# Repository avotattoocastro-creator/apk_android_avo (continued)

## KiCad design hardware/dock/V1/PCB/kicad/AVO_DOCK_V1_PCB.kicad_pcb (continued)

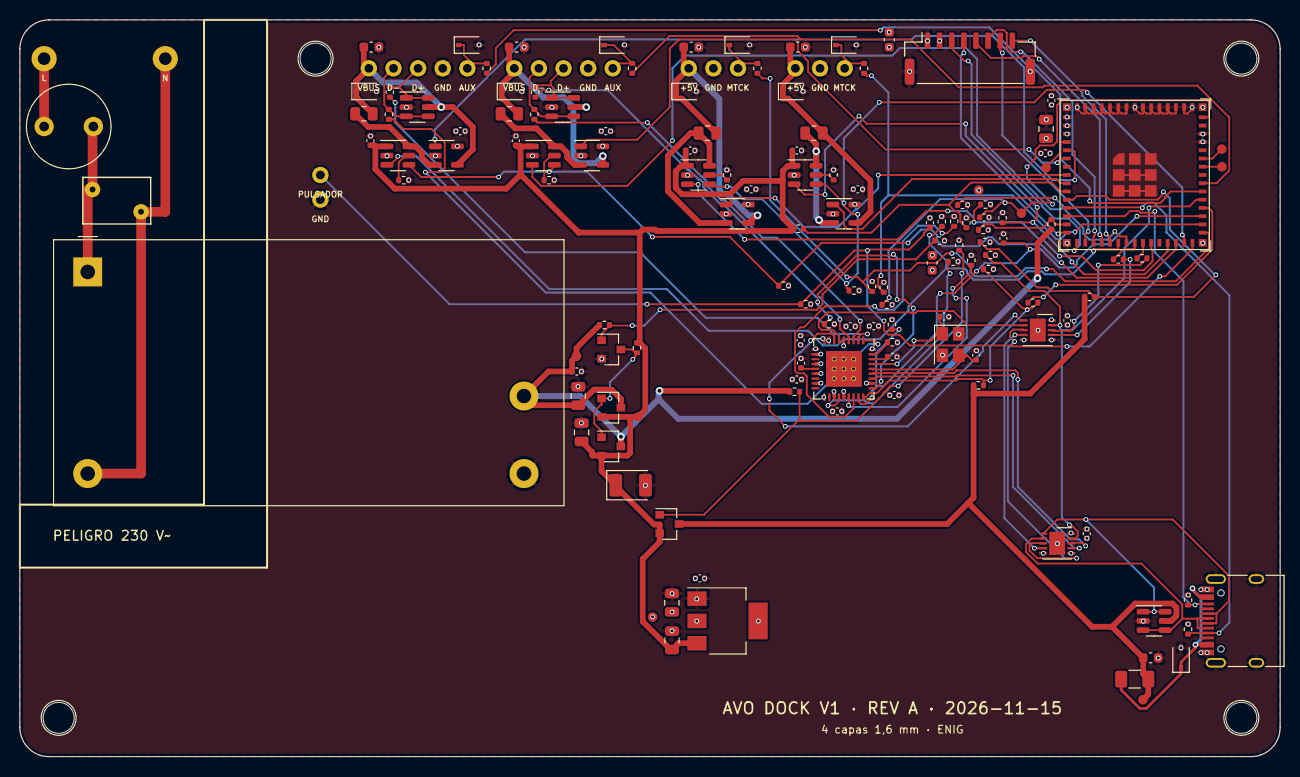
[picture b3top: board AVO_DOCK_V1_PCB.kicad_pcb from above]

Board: 4 copper layers, 130.0 x 76.0 mm, 160 parts (0 on the bottom side), 91 nets.

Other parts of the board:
H1, H2, H3, H4: TALADRO M3; AVO_Taladro_NPTH_D3.2

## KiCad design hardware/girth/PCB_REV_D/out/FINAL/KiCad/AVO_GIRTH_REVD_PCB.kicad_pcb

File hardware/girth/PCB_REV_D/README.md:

# AVO GIRTH · PCB REV D (cincha: ESP32-C6 + LSM6DSV16X + MMC5983MA + ADS1292)

Placa de 46 × 30 mm, 4 capas, generada desde Python (`fuente/`), ruteada en el CI (Freerouting 1.9) y completada con
`fuente/repair.py`. Comprobada en el CI con KiCad 9 (DRC, ERC y paridad).

- **Ficheros para JLCPCB:** `out/FINAL/` (Gerber zip, BOM, CPL, STEP, informe, SHA256SUMS).
- **Informe y decisiones:** `DOCS/INFORME_PCB_REV_D.md`. **Batería:** `DOCS/CONSUMO_BATERIA.md` (1000 mAh).
- **Firmware:** `firmware/girth/V0_6_0`.

Flujo:
1. `python3 fuente/place_revd.py` y después `python3 fuente/build.py`. Así se genera la placa de colocación.
2. El CI (`build-girth-pcb-revd.yml`) rutea y comprueba.
3. `python3 fuente/repair.py` completa las conexiones que falten y escribe `kicad/*_ruteado.kicad_pcb`, que el CI usa
   tal cual. Con `--src` se parte de otra placa y con `--rip` se rehacen redes.
4. `fuente/stitch_gnd.py --write` añade vías de cosido en las islas del relleno de F.Cu.

**Estado: VERIFICADO POR SOFTWARE · NO VERIFICADO EN HARDWARE REAL.**

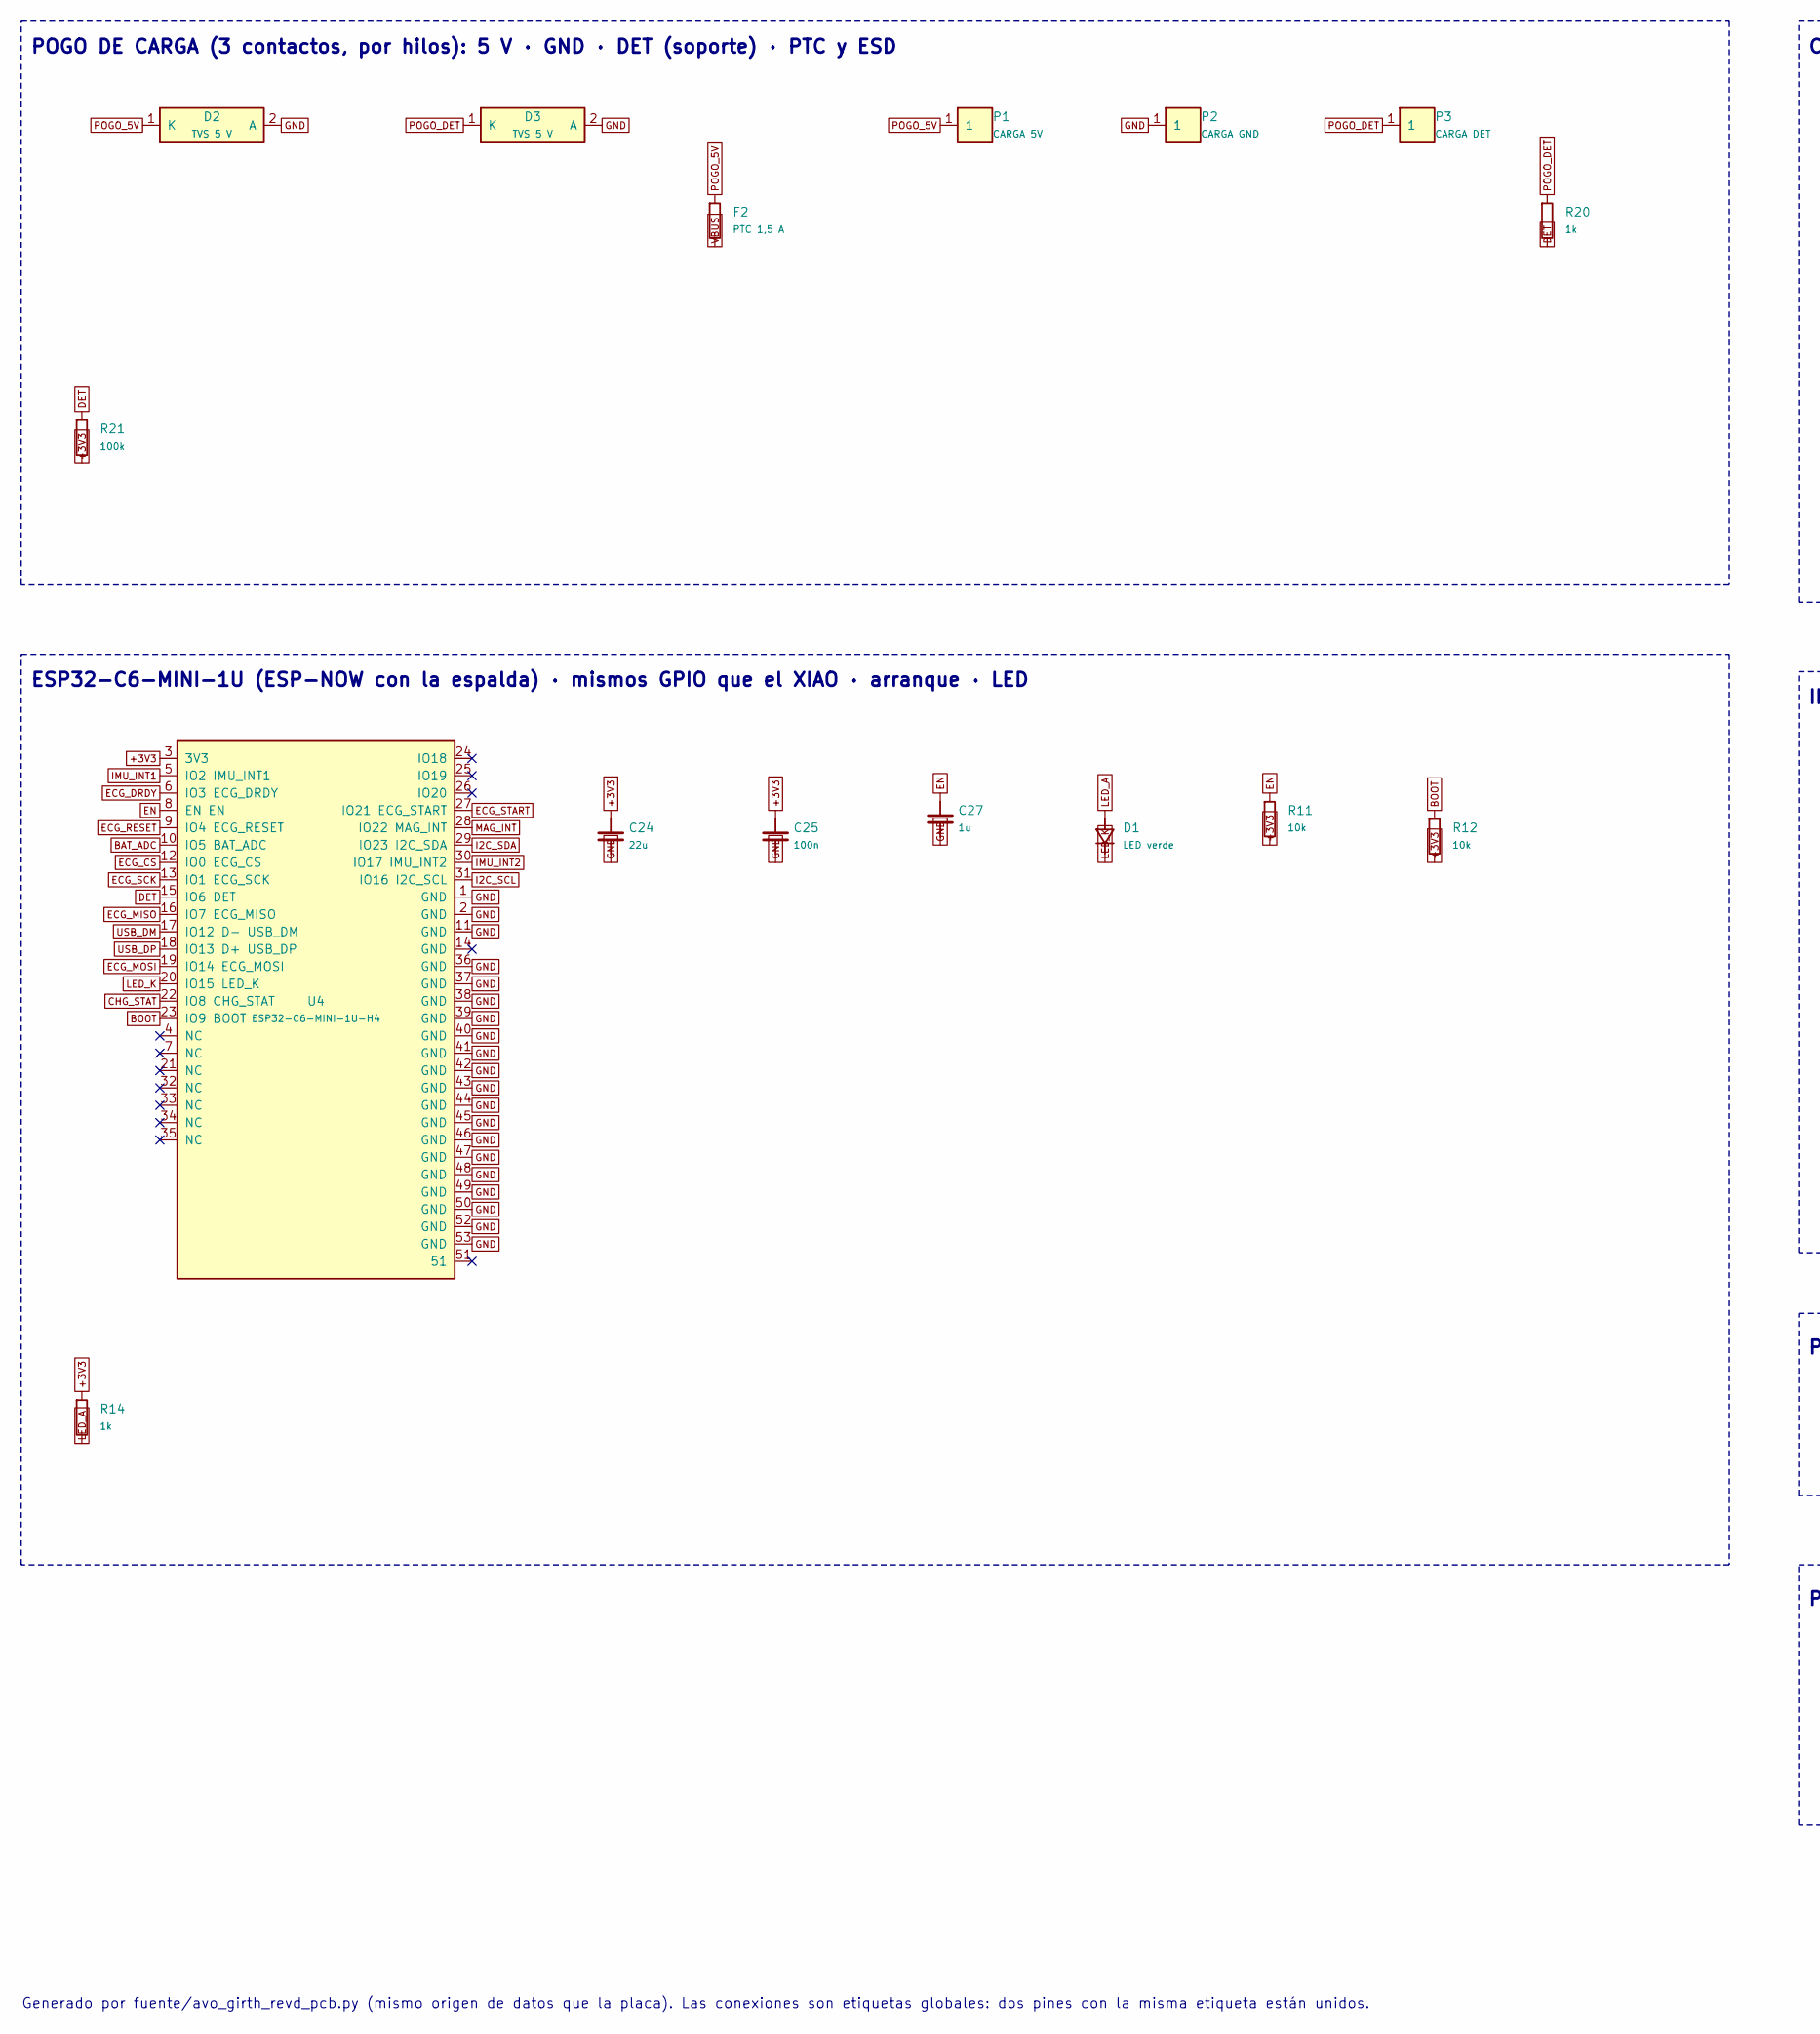
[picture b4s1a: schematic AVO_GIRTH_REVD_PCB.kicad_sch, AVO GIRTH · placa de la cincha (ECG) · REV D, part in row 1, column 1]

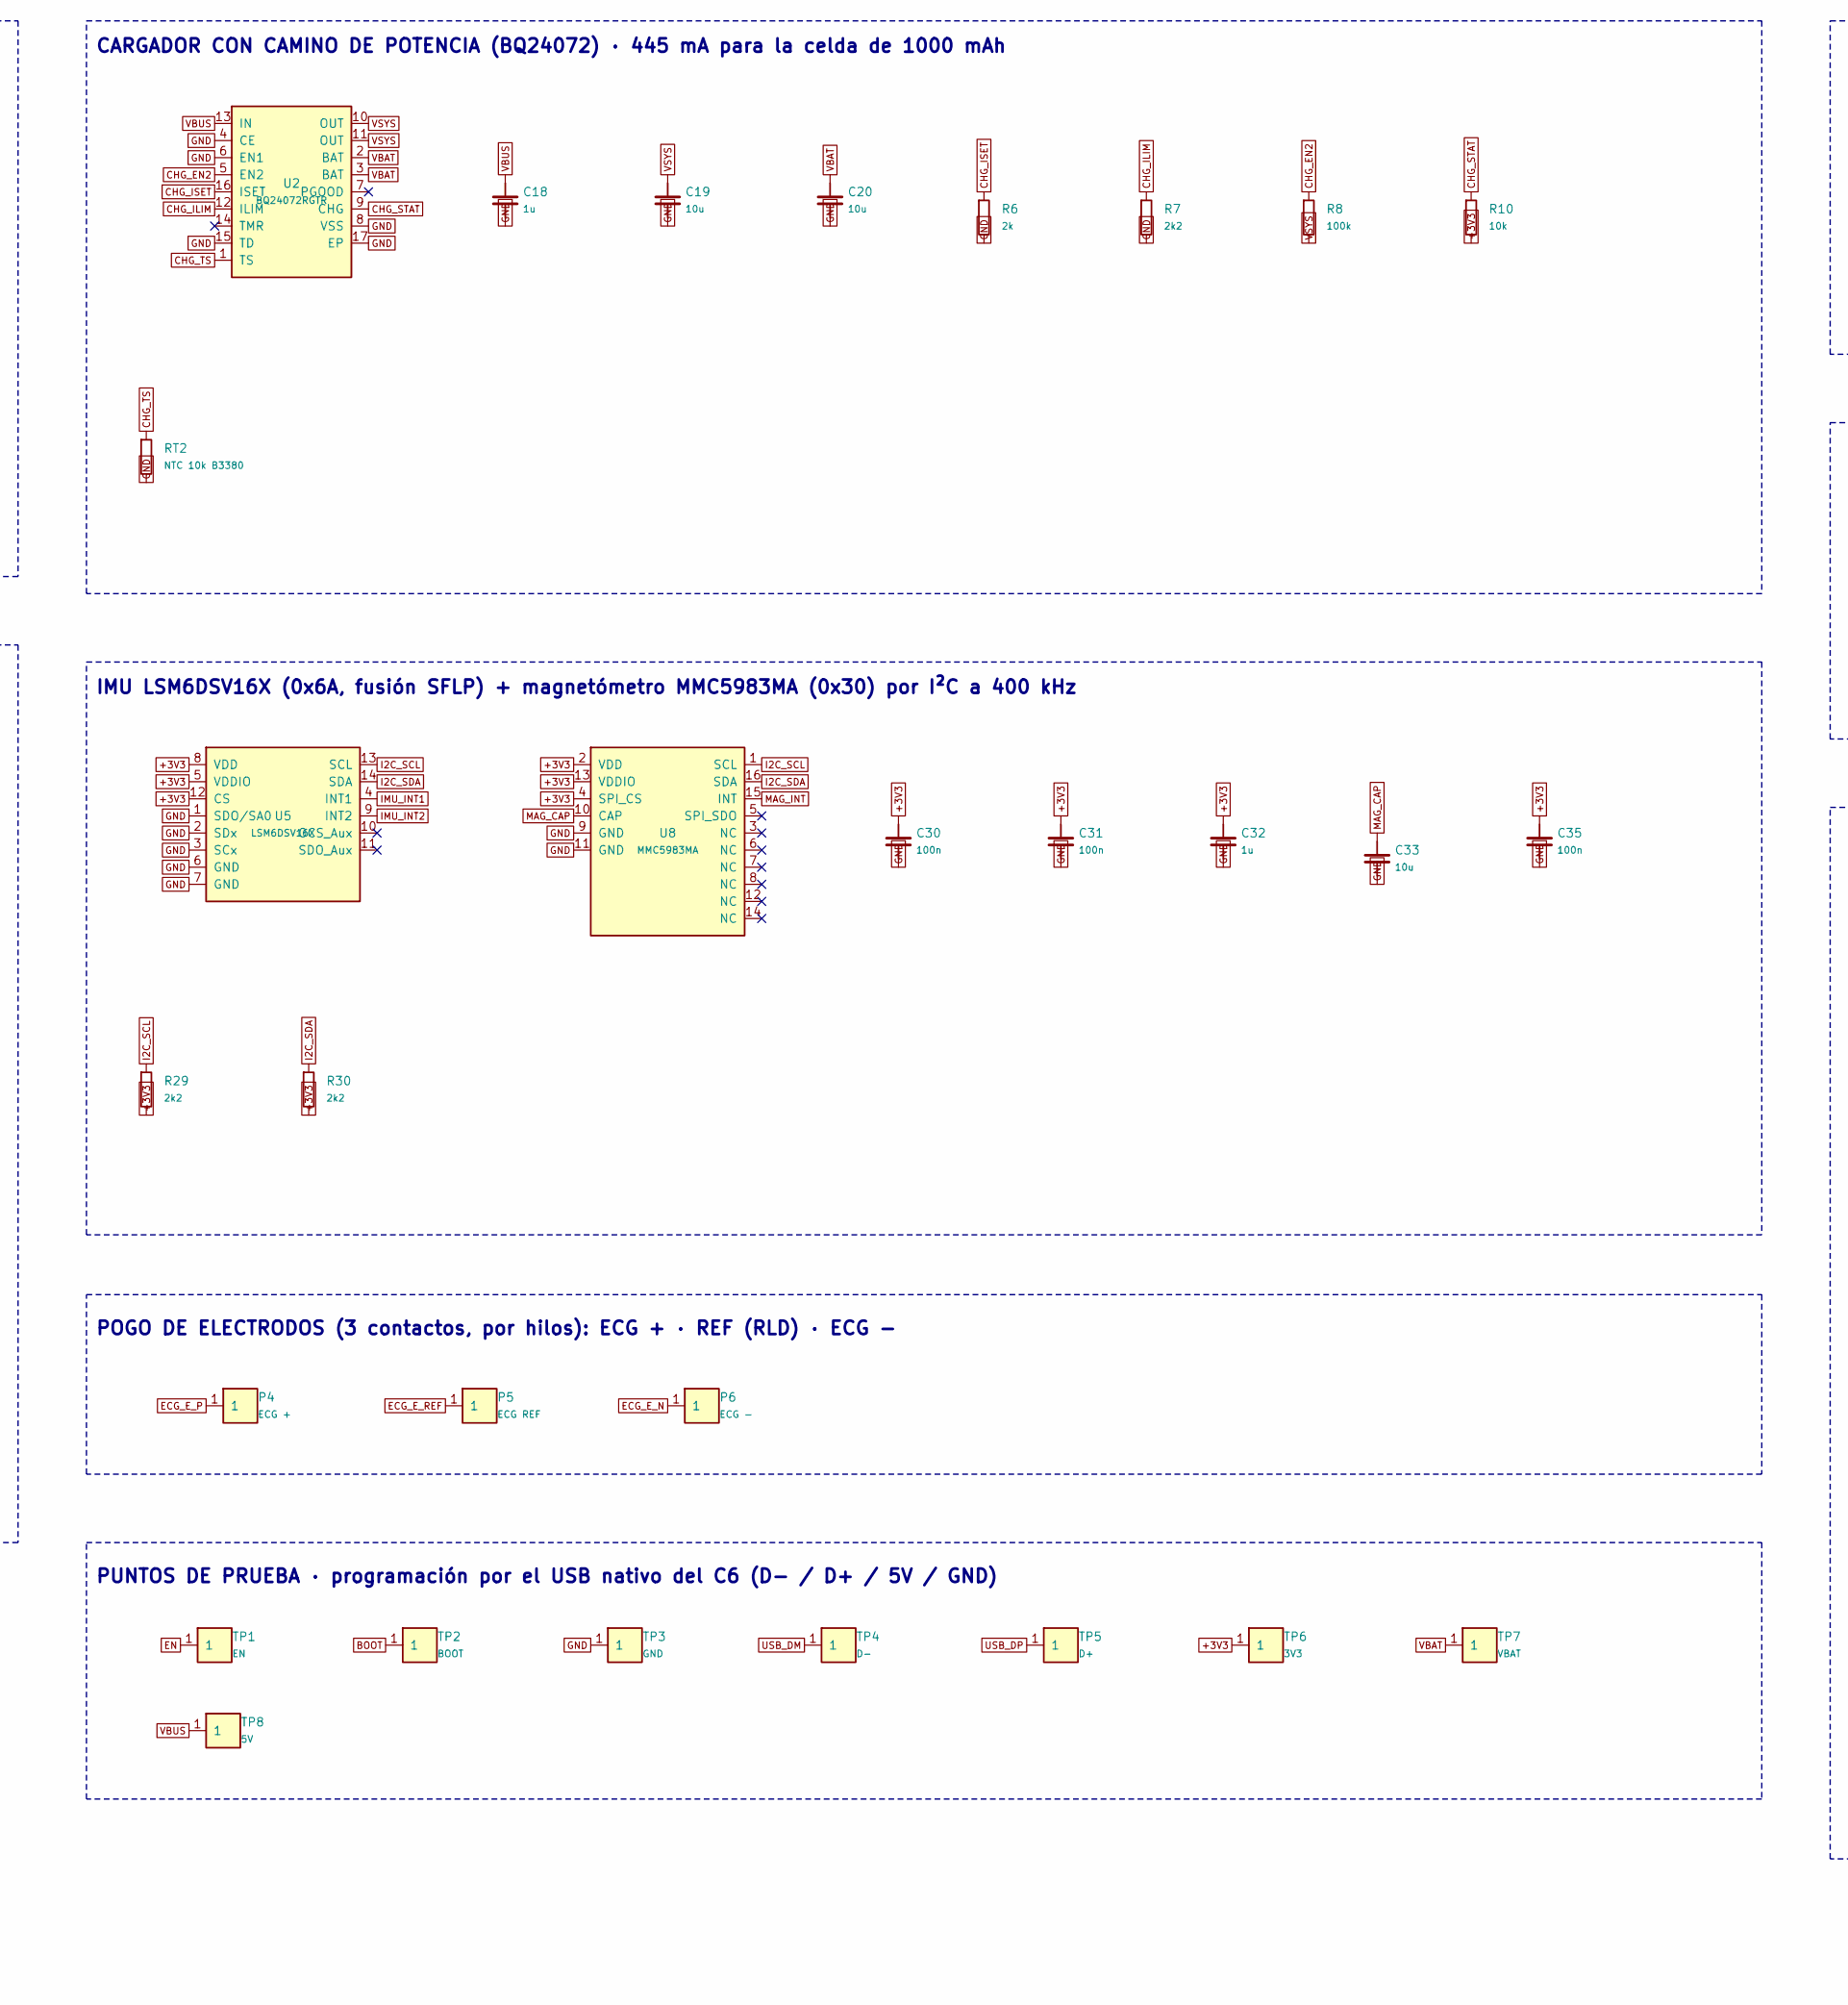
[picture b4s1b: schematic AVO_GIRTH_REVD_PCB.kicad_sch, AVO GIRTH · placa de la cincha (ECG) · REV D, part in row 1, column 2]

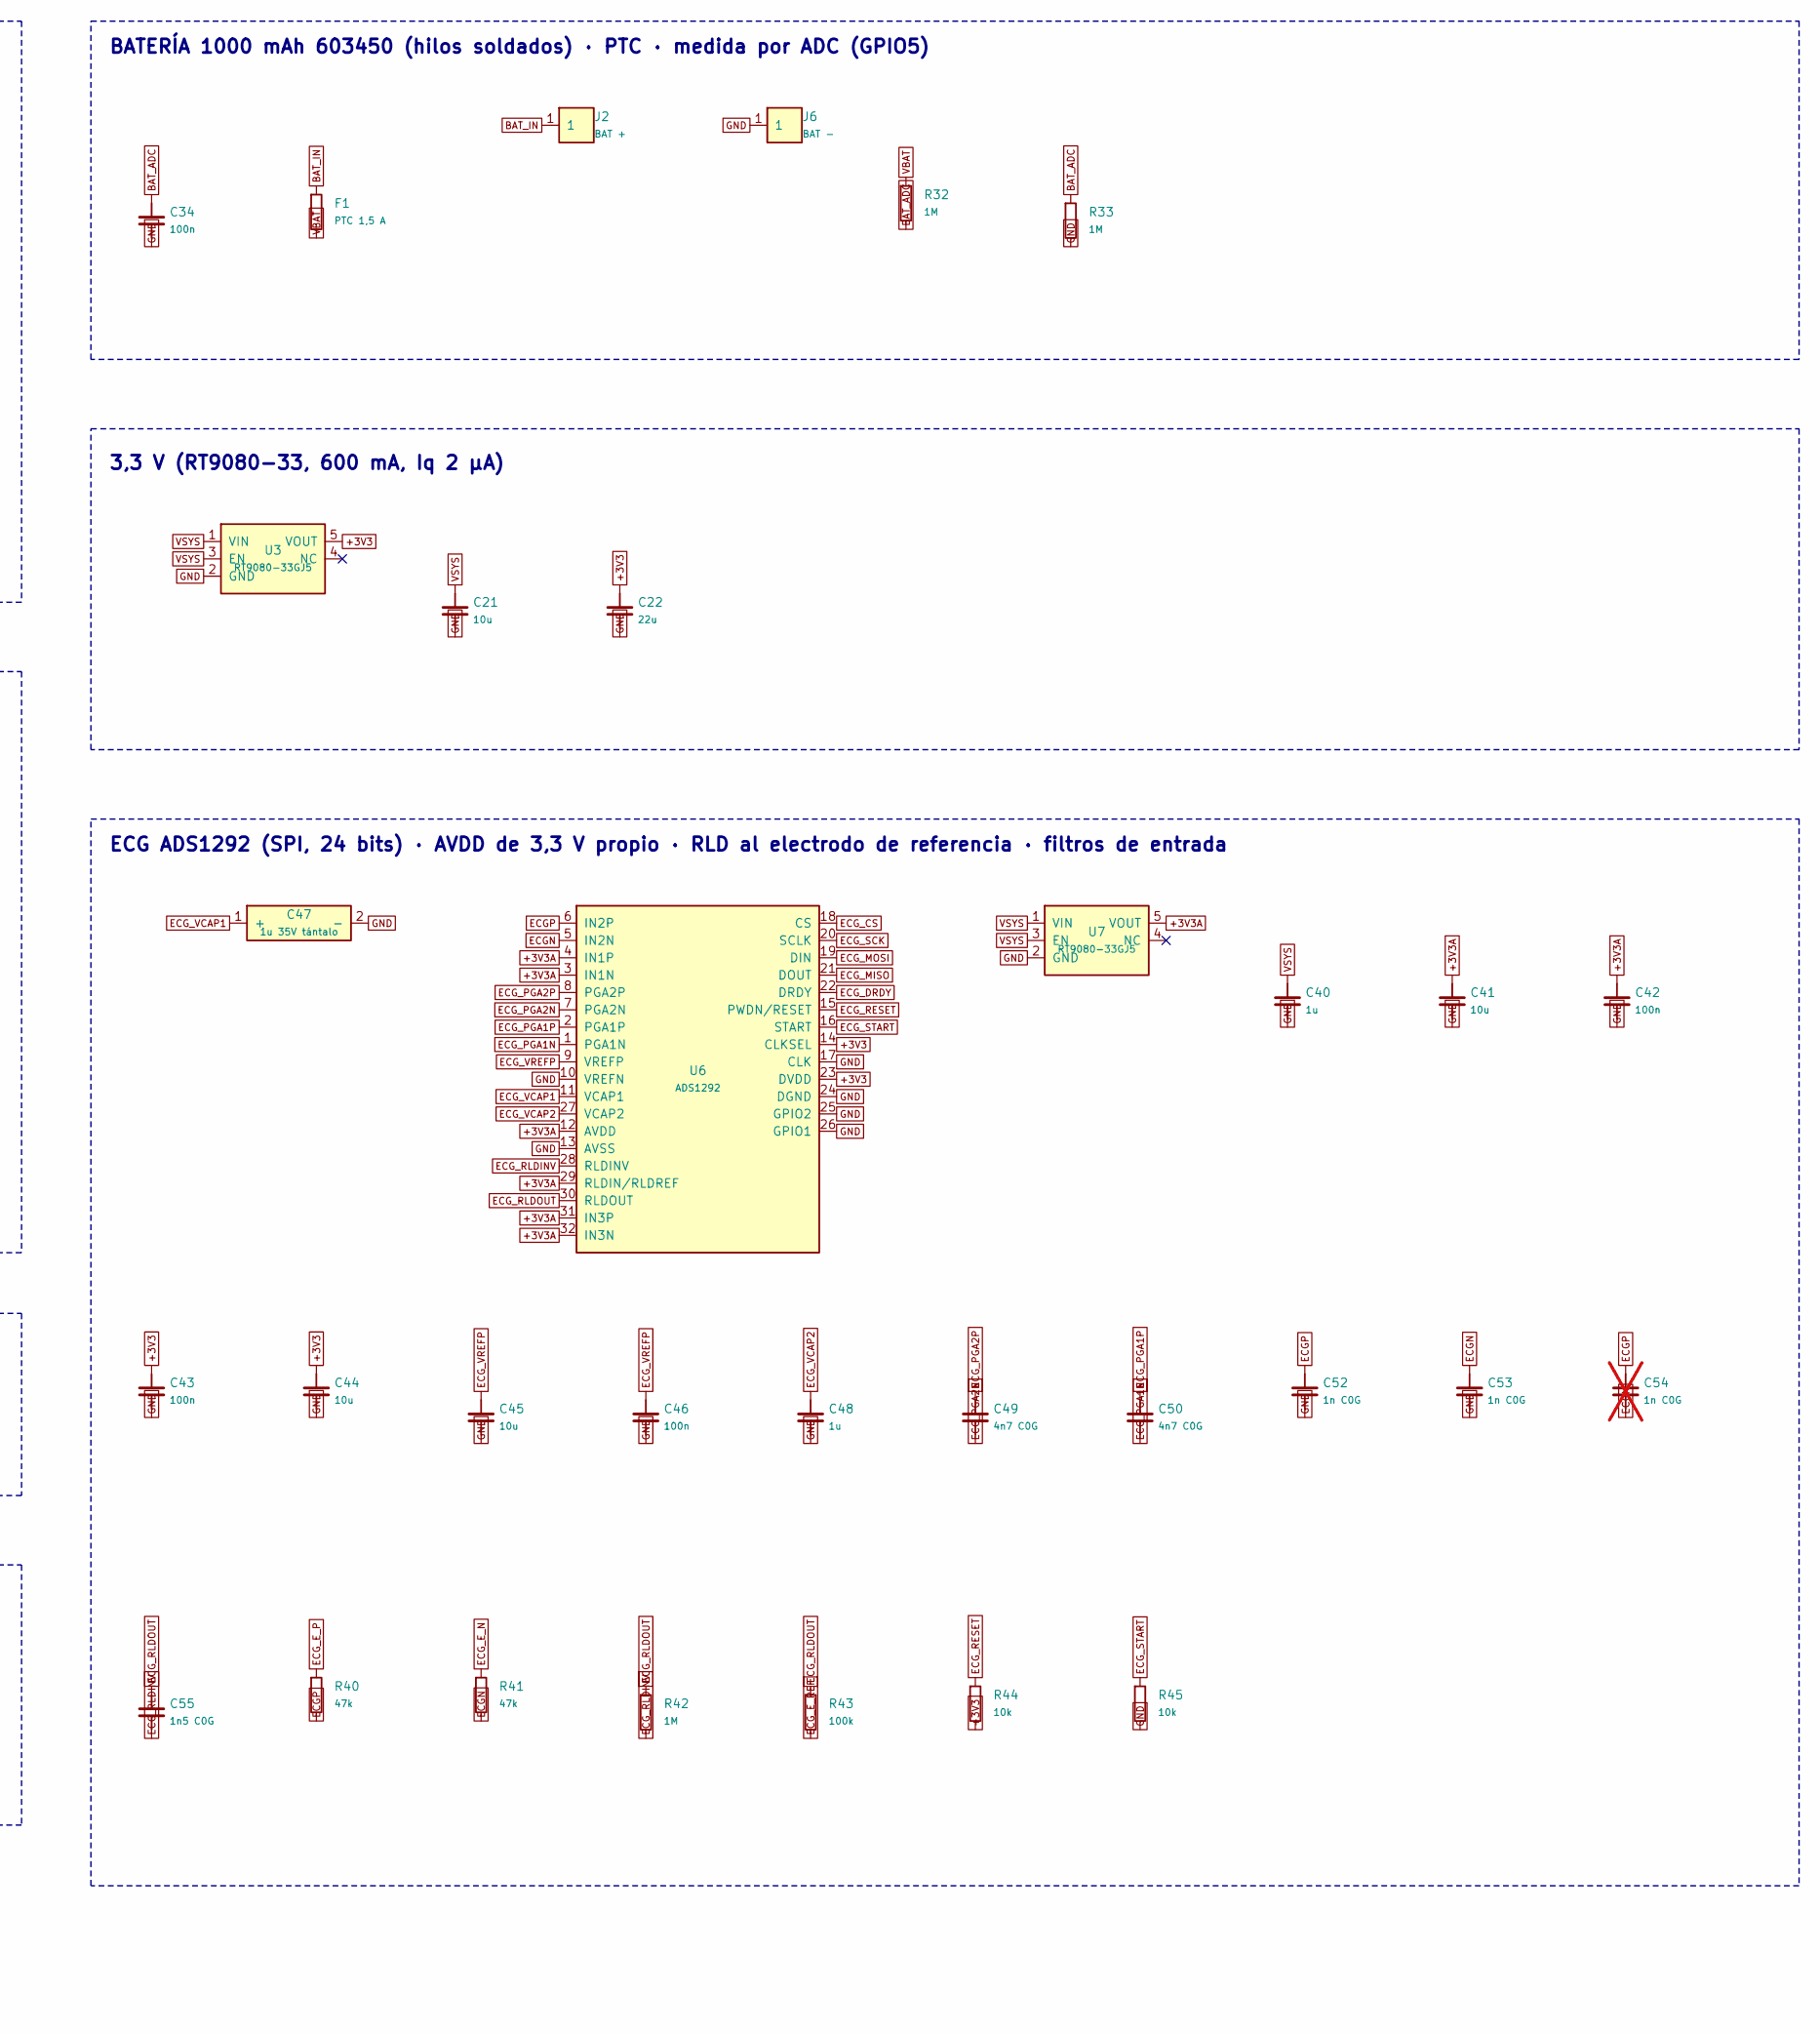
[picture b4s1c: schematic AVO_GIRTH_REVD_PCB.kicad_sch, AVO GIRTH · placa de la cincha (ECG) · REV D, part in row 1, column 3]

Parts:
C18, C27, C32, C40, C48: 1u; C_0402_1005Metric; LCSC C52923
C19, C20, C21, C33, C41, C44, C45: 10u; C_0603_1608Metric; LCSC C96446
C22, C24: 22u; C_0805_2012Metric; LCSC C45783
C25, C30, C31, C34, C35, C42, C43, C46: 100n; C_0402_1005Metric; LCSC C1525
C47: 1u 35V tántalo; CP_EIA-3528-21_Kemet-B; MPN TAJB105K035RNJ (Kyocera AVX); LCSC C7192
C49, C50: 4n7 C0G; C_0603_1608Metric; LCSC C85980
C52, C53: 1n C0G; C_0402_1005Metric; LCSC C53547
C54: 1n C0G; C_0402_1005Metric; LCSC C53547; not fitted
C55: 1n5 C0G; C_0402_1005Metric; LCSC C668348
D1: LED verde; LED_0603_1608Metric; LCSC C2286
D2, D3: TVS 5 V; D_SOD-323; MPN PESD5V0S1BA; LCSC C2827694
F1, F2: PTC 1,5 A; Fuse_1206_3216Metric; MPN SMD1206P150TF; LCSC C20802
J2: BAT +; WirePad_D1.5_Drill0.8
J6: BAT -; WirePad_D1.5_Drill0.8
P1: CARGA 5V; WirePad_D1.5_Drill0.8
P2: CARGA GND; WirePad_D1.5_Drill0.8
P3: CARGA DET; WirePad_D1.5_Drill0.8
P4: ECG +; WirePad_D1.5_Drill0.8
P5: ECG REF; WirePad_D1.5_Drill0.8
P6: ECG -; WirePad_D1.5_Drill0.8
R6: 2k; R_0402_1005Metric; LCSC C4109
R7, R29, R30: 2k2; R_0402_1005Metric; LCSC C25879
R8, R21, R43: 100k; R_0402_1005Metric; LCSC C25741
R10, R11, R12, R44, R45: 10k; R_0402_1005Metric; LCSC C25744
R14, R20: 1k; R_0402_1005Metric; LCSC C11702
R32, R33, R42: 1M; R_0402_1005Metric; LCSC C26083
R40, R41: 47k; R_0402_1005Metric; LCSC C25792
RT2: NTC 10k B3380; R_0402_1005Metric; MPN NCP15XH103F03RC; LCSC C77131
TP1: EN; TestPoint_Pad_D1.0mm
TP2: BOOT; TestPoint_Pad_D1.0mm
TP3: GND; TestPoint_Pad_D1.0mm
TP4: D-; TestPoint_Pad_D1.0mm
TP5: D+; TestPoint_Pad_D1.0mm
TP6: 3V3; TestPoint_Pad_D1.0mm
TP7: VBAT; TestPoint_Pad_D1.0mm
TP8: 5V; TestPoint_Pad_D1.0mm
U2: BQ24072RGTR; VQFN-16-1EP_3x3mm_P0.5mm_EP1.68x1.68mm_ThermalVias; MPN BQ24072RGTR; LCSC C140288
U3, U7: RT9080-33GJ5; SOT-23-5; MPN RT9080-33GJ5; LCSC C841192
U4: ESP32-C6-MINI-1U-H4; ESP32-C6-MINI-1U; MPN ESP32-C6-MINI-1U-H4 (alt. -N4); LCSC C20627095
U5: LSM6DSV16X; ST_LGA-14L_2.5x3mm_P0.5mm; MPN LSM6DSV16XTR (ST); LCSC C5267406
U6: ADS1292; AVO_TQFP-32_5x5mm_P0.5mm; MPN ADS1292IPBSR (TI, TQFP-32) · alt. ADS12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; LCSC C2651570
U8: MMC5983MA; MEMSIC_MMC5983MA_LGA-16_3x3mm_P0.5mm; MPN MMC5983MA (MEMSIC); LCSC C404329

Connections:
+3V3A: C41.1, C42.1, U6.3 (IN1N), U6.4 (IN1P), U6.12 (AVDD), U6.29 (RLDIN/RLDREF), U6.31 (IN3P), U6.32 (IN3N), U7.5 (VOUT)
BAT_ADC: C34.1, R32.2, R33.1, U4.10 (IO5 BAT_ADC)
BAT_IN: F1.1, J2.1
BOOT: R12.1, TP2.1, U4.23 (IO9 BOOT)
CHG_EN2: R8.1, U2.5 (EN2)
CHG_ILIM: R7.1, U2.12 (ILIM)
CHG_ISET: R6.1, U2.16 (ISET)
CHG_STAT: R10.1, U2.9 (CHG), U4.22 (IO8 CHG_STAT)
CHG_TS: RT2.1, U2.1 (TS)
DET: R20.2, R21.1, U4.15 (IO6 DET)
ECGN: C53.1, C54.2, R41.2, U6.5 (IN2N)
ECGP: C52.1, C54.1, R40.2, U6.6 (IN2P)
ECG_CS: U4.12 (IO0 ECG_CS), U6.18 (CS)
ECG_DRDY: U4.6 (IO3 ECG_DRDY), U6.22 (DRDY)
ECG_E_N: P6.1, R41.1
ECG_E_P: P4.1, R40.1
ECG_E_REF: P5.1, R43.2
ECG_MISO: U4.16 (IO7 ECG_MISO), U6.21 (DOUT)
ECG_MOSI: U4.19 (IO14 ECG_MOSI), U6.19 (DIN)
ECG_PGA1N: C50.2, U6.1 (PGA1N)
ECG_PGA1P: C50.1, U6.2 (PGA1P)
ECG_PGA2N: C49.2, U6.7 (PGA2N)
ECG_PGA2P: C49.1, U6.8 (PGA2P)
ECG_RESET: R44.1, U4.9 (IO4 ECG_RESET), U6.15 (PWDN/RESET)
ECG_RLDINV: C55.2, R42.2, U6.28 (RLDINV)
ECG_RLDOUT: C55.1, R42.1, R43.1, U6.30 (RLDOUT)
ECG_SCK: U4.13 (IO1 ECG_SCK), U6.20 (SCLK)
ECG_START: R45.1, U4.27 (IO21 ECG_START), U6.16 (START)
ECG_VCAP1: C47.1 (+), U6.11 (VCAP1)
ECG_VCAP2: C48.1, U6.27 (VCAP2)
ECG_VREFP: C45.1, C46.1, U6.9 (VREFP)
EN: C27.1, R11.1, TP1.1, U4.8 (EN EN)
GND: C18.2, C19.2, C20.2, C21.2, C22.2, C24.2, C25.2, C27.2, C30.2, C31.2, C32.2, C33.2, C34.2, C35.2, C40.2, C41.2, C42.2, C43.2, C44.2, C45.2, C46.2, C47.2 (−), C48.2, C52.2, C53.2, D2.2 (A), D3.2 (A), J6.1, P2.1, R6.2, R7.2, R33.2, R45.2, RT2.2, TP3.1, U2.4 (CE), U2.6 (EN1), U2.8 (VSS), U2.15 (TD), U2.17 (EP), U3.2 (GND), U4.1 (GND), U4.2 (GND), U4.11 (GND), U4.36 (GND), U4.37 (GND), U4.38 (GND), U4.39 (GND), U4.40 (GND), U4.41 (GND), U4.42 (GND), U4.43 (GND), U4.44 (GND), U4.45 (GND), U4.46 (GND), U4.47 (GND), U4.48 (GND), U4.49 (GND), U4.50 (GND), U4.52 (GND), U4.53 (GND), U5.1 (SDO/SA0), U5.2 (SDx), U5.3 (SCx), U5.6 (GND), U5.7 (GND), U6.10 (VREFN), U6.13 (AVSS), U6.17 (CLK), U6.24 (DGND), U6.25 (GPIO2), U6.26 (GPIO1), U7.2 (GND), U8.9 (GND), U8.11 (GND); also elsewhere on the board
I2C_SCL: R29.1, U4.31 (IO16 I2C_SCL), U5.13 (SCL), U8.1 (SCL)
I2C_SDA: R30.1, U4.29 (IO23 I2C_SDA), U5.14 (SDA), U8.16 (SDA)
IMU_INT1: U4.5 (IO2 IMU_INT1), U5.4 (INT1)
IMU_INT2: U4.30 (IO17 IMU_INT2), U5.9 (INT2)
LED_D1: D1.2 (A), R14.2; also elsewhere on the board
LED_EN: U4.24 (IO18); also elsewhere on the board
MAG_CAP: C33.1, U8.10 (CAP)
MAG_INT: U4.28 (IO22 MAG_INT), U8.15 (INT)
POGO_5V: D2.1 (K), F2.1, P1.1
POGO_DET: D3.1 (K), P3.1, R20.1
USB_DM: TP4.1, U4.17 (IO12 D- USB_DM)
USB_DP: TP5.1, U4.18 (IO13 D+ USB_DP)
VBAT: C20.1, F1.2, R32.1, TP7.1, U2.2 (BAT), U2.3 (BAT)
VBUS: C18.1, F2.2, TP8.1, U2.13 (IN)
VSYS: C19.1, C21.1, C40.1, R8.2, U2.10 (OUT), U2.11 (OUT), U3.1 (VIN), U3.3 (EN), U7.1 (VIN), U7.3 (EN); also elsewhere on the board

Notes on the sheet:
ECG ADS1292 (SPI, 24 bits) · AVDD de 3,3 V propio · RLD al electrodo de referencia · filtros de entrada
POGO DE CARGA (3 contactos, por hilos): 5 V · GND · DET (soporte) · PTC y ESD
CARGADOR CON CAMINO DE POTENCIA (BQ24072) · 445 mA para la celda de 1000 mAh
3,3 V (RT9080-33, 600 mA, Iq 2 µA)
ESP32-C6-MINI-1U (ESP-NOW con la espalda) · mismos GPIO que el XIAO · arranque · LED
IMU LSM6DSV16X (0x6A, fusión SFLP) + magnetómetro MMC5983MA (0x30) por I²C a 400 kHz
BATERÍA 1000 mAh 603450 (hilos soldados) · PTC · medida por ADC (GPIO5)
POGO DE ELECTRODOS (3 contactos, por hilos): ECG + · REF (RLD) · ECG −
PUNTOS DE PRUEBA · programación por el USB nativo del C6 (D− / D+ / 5V / GND)
Generado por fuente/avo_girth_revd_pcb.py (mismo origen de datos que la placa). Las conexiones son etiquetas globales: dos pines con la misma etiqueta están unidos.

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
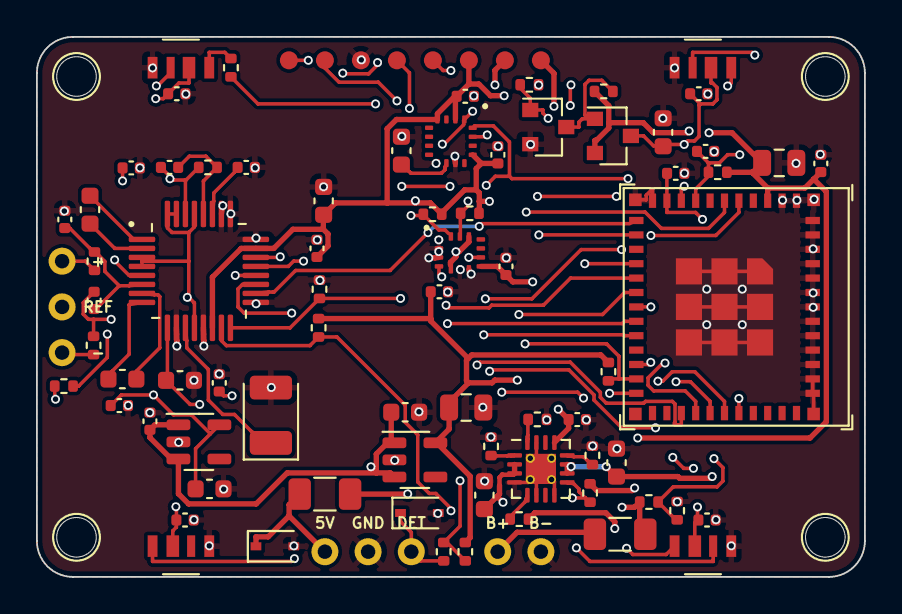
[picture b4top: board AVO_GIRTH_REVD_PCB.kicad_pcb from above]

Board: 4 copper layers, 46.0 x 30.0 mm, 93 parts (0 on the bottom side), 55 nets.

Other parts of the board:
C60: 10u; C_0603_1608Metric
C61, C62, C63, C64: 100n; C_0402_1005Metric
D10, D11, D12, D13: SK6812SIDE-A; AVO_SK6812SIDE-A_4.0x1.6mm
H1, H2, H3, H4: TALADRO M2; AVO_Taladro_NPTH_D2.2
Q1: AO3401A; SOT-23
Q2: 2N7002; SOT-23
R15, R16: 100k; R_0402_1005Metric

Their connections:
GND: C60.2, C61.2, C62.2, C63.2, C64.2, D10.4, D11.4, D12.4, D13.4, Q2.2, R16.2; also elsewhere on the board
LED_D1: D10.1; also elsewhere on the board
LED_D2: D10.3, D11.1
LED_D3: D11.3, D12.1
LED_D4: D12.3, D13.1
LED_EN: Q2.1, R16.1; also elsewhere on the board
LED_G: Q1.1, Q2.3, R15.2
VLED: C60.1, C61.1, C62.1, C63.1, C64.1, D10.2, D11.2, D12.2, D13.2, Q1.3
VSYS: Q1.2, R15.1; also elsewhere on the board

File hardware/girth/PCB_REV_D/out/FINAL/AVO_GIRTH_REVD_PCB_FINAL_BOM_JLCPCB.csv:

Comment,Designator,Footprint,LCSC Part #
"PTC 1,5 A","F1,F2",Fuse_1206_3216Metric,C20802
TVS 5 V,"D2,D3",D_SOD-323,C2827694
1k,R20,R_0402_1005Metric,C11702
100k,"R8,R15,R16,R21,R43",R_0402_1005Metric,C25741
BQ24072RGTR,U2,VQFN-16-1EP_3x3mm_P0.5mm_EP1.68x1.68mm_ThermalVias,C140288
1u,"C18,C27,C32,C40,C48",C_0402_1005Metric,C52923
10u,"C19,C20,C21,C33,C41,C44,C45,C60",C_0603_1608Metric,C96446
2k,R6,R_0402_1005Metric,C4109
2k2,"R7,R29,R30",R_0402_1005Metric,C25879
NTC 10k B3380,RT2,R_0402_1005Metric,C77131
10k,"R10,R11,R12,R44,R45",R_0402_1005Metric,C25744
1M,"R32,R33,R42",R_0402_1005Metric,C26083
100n,"C25,C30,C31,C34,C35,C42,C43,C46,C61,C62,C63,C64",C_0402_1005Metric,C1525
RT9080-33GJ5,"U3,U7",SOT-23-5,C841192
22u,"C22,C24",C_0805_2012Metric,C45783
ESP32-C6-MINI-1U-H4,U4,ESP32-C6-MINI-1U,C20627095
22R,R14,R_0402_1005Metric,C25092
AO3401A,Q1,SOT-23,C15127
2N7002,Q2,SOT-23,C8545
SK6812SIDE-A,"D10,D11,D12,D13",AVO_SK6812SIDE-A_4.0x1.6mm,C5378721
LSM6DSV16X,U5,ST_LGA-14L_2.5x3mm_P0.5mm,C5267406
MMC5983MA,U8,MEMSIC_MMC5983MA_LGA-16_3x3mm_P0.5mm,C404329
ADS1292,U6,AVO_TQFP-32_5x5mm_P0.5mm,C2651570
1u 35V tántalo,C47,CP_EIA-3528-21_Kemet-B,C7192
4n7 C0G,"C49,C50",C_0603_1608Metric,C85980
47k,"R40,R41",R_0402_1005Metric,C25792
1n C0G,"C52,C53",C_0402_1005Metric,C53547
1n5 C0G,C55,C_0402_1005Metric,C668348
